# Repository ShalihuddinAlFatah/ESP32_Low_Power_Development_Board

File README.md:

# ESP32_Low_Power_Development_Board

Simple ESP32 development board specifically designed for low power project. 
1. This PCB doesn't have on-board USB to TTL and any LED light. It allows to accurately measure current consumption of your low power IoT project. 
2. Each I/O has 2 pin headers, one for connecting to peripherals and one for troubleshooting purpose (Logic analyzer, oscilloscope, etc).
3. Clearance and creepage minimum 0.2mm (IPC-2221A).
4. Boot and reset button.  

You can find the overview of the schematic and the PCB file in 'Picture and PDF' directory

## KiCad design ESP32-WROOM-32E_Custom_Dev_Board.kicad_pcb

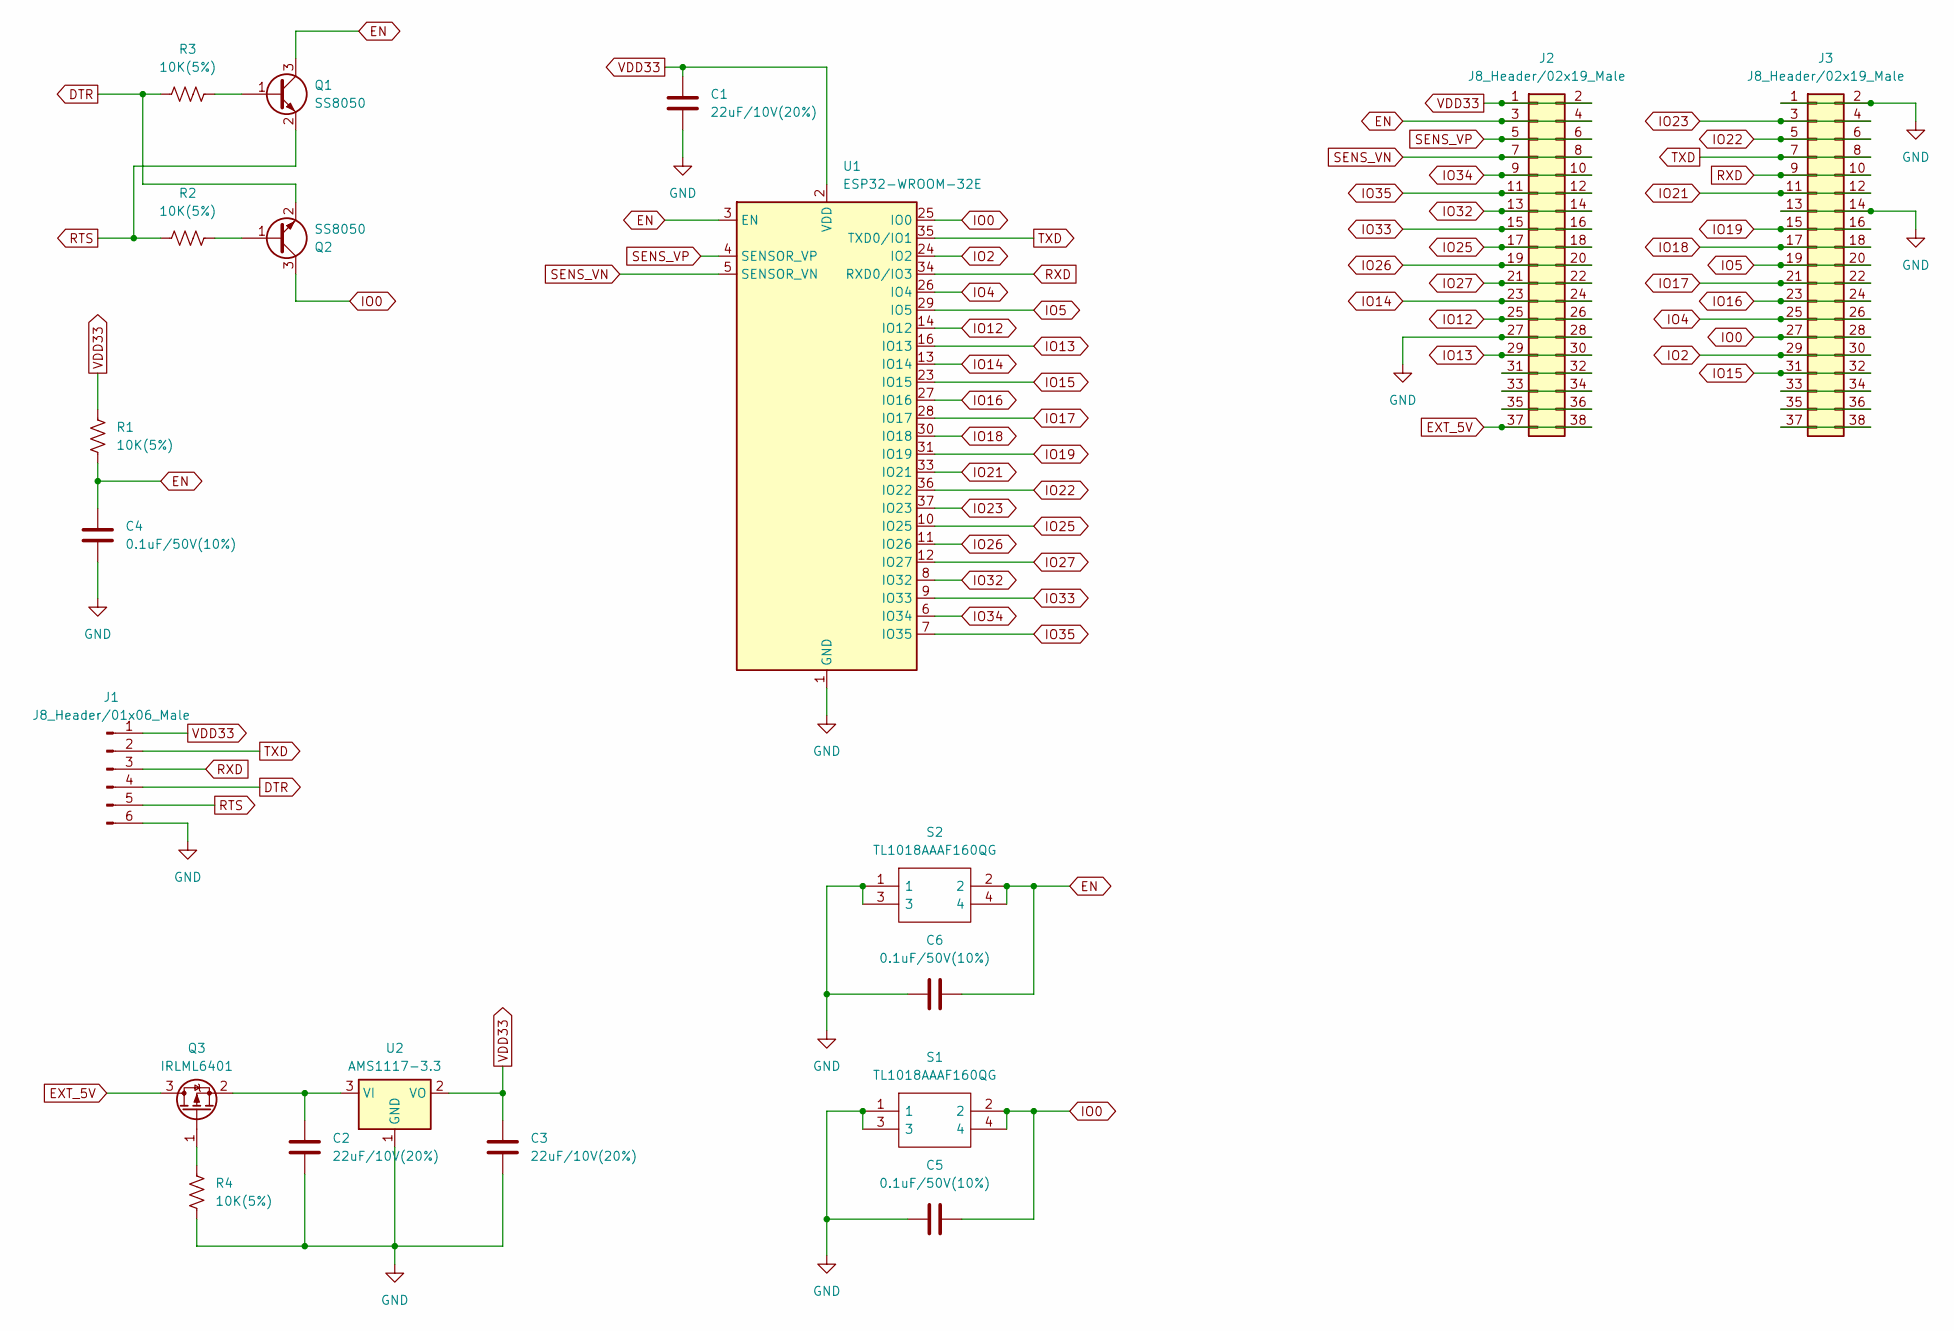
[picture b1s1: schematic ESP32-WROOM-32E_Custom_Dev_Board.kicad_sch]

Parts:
C1, C2, C3: 22uF/10V(20%); C_0805_2012Metric_Pad1.18x1.45mm_HandSolder
C4, C5, C6: 0.1uF/50V(10%); C_0805_2012Metric_Pad1.18x1.45mm_HandSolder
J1: J8_Header/01x06_Male; PinHeader_1x06_P2.54mm_Vertical
J2, J3: J8_Header/02x19_Male; PinHeader_2x19_P2.54mm_Vertical
Q1, Q2: SS8050; SOT-23
Q3: IRLML6401; SOT-23
R1, R2, R3, R4: 10K(5%); R_0805_2012Metric_Pad1.20x1.40mm_HandSolder
S1, S2: TL1018AAAF160QG; Mouser Part Number 612-TL1018AAAF160QG
U1: ESP32-WROOM-32E
U2: AMS1117-3.3; SOT-223-3_TabPin2

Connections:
DTR: J1.4, Q2.2 (E), R3.1
EN: C4.1, C6.2, J2.3, J2.4, Q1.3 (C), R1.2, S2.2, S2.4, U1.3 (EN)
EXT_5V: J2.37, J2.38, Q3.3 (D)
GND: C1.2, C2.2, C3.2, C4.2, C5.1, C6.1, J1.6, J2.27, J2.28, J3.1, J3.2, J3.13, J3.14, R4.2, S1.1, S1.3, S2.1, S2.3, U1.1 (GND), U1.15 (GND), U1.38 (GND), U1.39 (GND), U2.1 (GND)
IO0: C5.2, J3.27, J3.28, Q2.3 (C), S1.2, S1.4, U1.25 (IO0)
IO2: J3.29, J3.30, U1.24 (IO2)
IO4: J3.25, J3.26, U1.26 (IO4)
IO5: J3.19, J3.20, U1.29 (IO5)
IO12: J2.25, J2.26, U1.14 (IO12)
IO13: J2.29, J2.30, U1.16 (IO13)
IO14: J2.23, J2.24, U1.13 (IO14)
IO15: J3.31, J3.32, U1.23 (IO15)
IO16: J3.23, J3.24, U1.27 (IO16)
IO17: J3.21, J3.22, U1.28 (IO17)
IO18: J3.17, J3.18, U1.30 (IO18)
IO19: J3.15, J3.16, U1.31 (IO19)
IO21: J3.11, J3.12, U1.33 (IO21)
IO22: J3.5, J3.6, U1.36 (IO22)
IO23: J3.3, J3.4, U1.37 (IO23)
IO25: J2.17, J2.18, U1.10 (IO25)
IO26: J2.19, J2.20, U1.11 (IO26)
IO27: J2.21, J2.22, U1.12 (IO27)
IO32: J2.13, J2.14, U1.8 (IO32)
IO33: J2.15, J2.16, U1.9 (IO33)
IO34: J2.9, J2.10, U1.6 (IO34)
IO35: J2.11, J2.12, U1.7 (IO35)
unnamed: J2.31, J2.32
unnamed: J2.33, J2.34
unnamed: J2.35, J2.36
unnamed: J3.33, J3.34
unnamed: J3.35, J3.36
unnamed: J3.37, J3.38
unnamed: Q1.1 (B), R3.2
unnamed: Q2.1 (B), R2.2
unnamed: Q3.1 (G), R4.1
unnamed: C2.1, Q3.2 (S), U2.3 (VI)
RTS: J1.5, Q1.2 (E), R2.1
RXD: J1.3, J3.9, J3.10, U1.34 (RXD0/IO3)
SENS_VN: J2.7, J2.8, U1.5 (SENSOR_VN)
SENS_VP: J2.5, J2.6, U1.4 (SENSOR_VP)
TXD: J1.2, J3.7, J3.8, U1.35 (TXD0/IO1)
VDD33: C1.1, C3.1, J1.1, J2.1, J2.2, R1.1, U1.2 (VDD), U2.2 (VO)

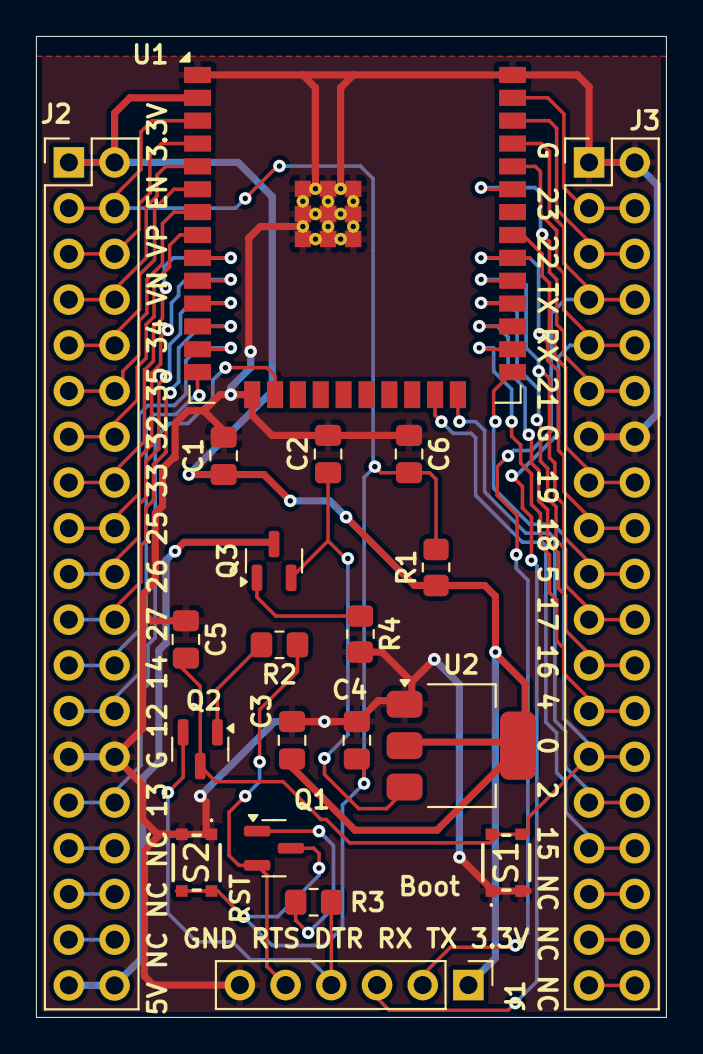
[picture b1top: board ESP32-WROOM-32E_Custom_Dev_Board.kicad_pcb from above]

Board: 2 copper layers, 35.0 x 54.5 mm, 20 parts (0 on the bottom side), 42 nets.

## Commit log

2025-03-15 Update LICENSE
2025-06-04 Rename ESP32-WROOM-32E_Custom_Dev_Board.pdf to ESP32-WROOM-32E_Custom_Dev_Board_Schematic.pdf
